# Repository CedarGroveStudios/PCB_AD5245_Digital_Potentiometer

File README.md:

# PCB_AD5245_Digital_Potentiometer
### _A small breakout board and CircuitPython driver for the 10K AD5245 digital potentiometer._

The AD5245 Digital Potentiometer breakout board is a simple implementation of the Analog Devices' I2C, 10K-ohm chip. The potentiometer sports 256 resistance steps and can work with a power source from 2.7v to 5.5v. The pins act similarly to a passive resistive potentiometer, but require that voltages placed on any of the three pins not exceed the power supply voltage or drop below ground potential.

A CircuitPython library is available in the code folder.

OSH Park project: https://oshpark.com/shared_projects/WcYMJx7L

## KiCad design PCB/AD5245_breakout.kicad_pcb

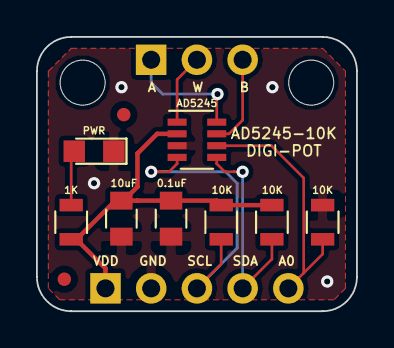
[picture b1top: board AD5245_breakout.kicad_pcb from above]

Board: 2 copper layers, 17.8 x 15.2 mm, 10 parts (0 on the bottom side), 9 nets.

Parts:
C1: 0.1uF; C_0805
C2: 10uF; C_0805
D1: PWR; LED_0805
J1: BKOUT_PINS; Pin_Header_Straight_1x05_Pitch2.54mm_no_silk
J2: POTENTIOMETER; Pin_Header_Straight_1x03_Pitch2.54mm_no_silk
R1, R2, R3: 10K; R_0805
R4: 1K; R_0805
U1: AD5245; SOT-23-8

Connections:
+3V3: C1.1, C2.1, J1.1, R1.2, R2.2, R4.2, U1.2
/A: J2.1, U1.8
/A0: J1.5, R3.2, U1.6
/B: J2.3, U1.7
/SCL: J1.3, R1.1, U1.4
/SDA: J1.4, R2.1, U1.5
/W: J2.2, U1.1
GND: C1.2, C2.2, D1.1, J1.2, R3.1, U1.3
unnamed: D1.2, R4.1

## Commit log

2022-11-15 initial repo load
